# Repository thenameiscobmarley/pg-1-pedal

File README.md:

# PG-1 pedal

A DIY stereo audio pedal built around a **Daisy Seed3**, in a white Hammond 1590XX from Tayda. A 2.4" colour
touchscreen, four endless push-knobs, three footswitches and a chain of sound tools:

`in -> hum + hiss (with learn) -> input auto-level -> dynamic eq -> compressor -> multiband -> clarity + bass ->
saturation -> de-harsh -> stereo width -> takeback -> quiet loudness -> [bypass] -> ear + speaker safety -> out`

plus a visualizer, health checks (it tells you when something is wrong), 8 saved configs, a fair level-matched
A/B footswitch, and everything remembered over power-off.

The same core code runs on the pedal and in a **Carla / VST3 plugin** with a real-size 3D model of the pedal, so you
can try every screen and sound on a PC first.

## What's where

| Folder | |
|---|---|
| `PG-Pedal-1/01-Questions-and-Specs` | the spec |
| `PG-Pedal-1/02-Parts-and-Cart` | Tayda cart files + parts list (with the few parts Tayda doesn't sell) |
| `PG-Pedal-1/03-Drill-Template` | drill positions for drill.taydakits.com |
| `PG-Pedal-1/04-Top-Artwork` | the UV print (CMYK PDF for Tayda) and previews |
| `PG-Pedal-1/05-Wiring-and-Schematics` | **wiring-diagram.png** (every wire + both ground chains), layout drawings, WIRING.md |
| `PG-Pedal-1/06-Firmware-DaisySeed` | the firmware (`pg1/`) and its shared core (`pg1/core/`) |
| `PG-Pedal-1/10-Carla-Plugin` | the JUCE plugin with the 3D pedal |
| `PG-Pedal-1/11-Wiring-Bench` | `wiring-bench.html`: practise the wiring in a browser; a virtual pedal tells you what's wrong |
| `_Tools/pg_generate.py` | one script makes the drill table, artwork, drawings and the splash logo from the geometry at its top |
| `_Tools/tayda_upload.py` | uploads the drill + print designs to drill.taydakits.com (asks for your Tayda login) |
| `third_party/HardwareKit` | the 3D hardware UI module the plugin uses (Apache-2.0) |

## Building

Firmware (Linux):

```
git submodule update --init           # libDaisy v9.0.0 + DaisySP
cd PG-Pedal-1/06-Firmware-DaisySeed
(cd libDaisy && make -j"$(nproc)") && (cd DaisySP && make -j"$(nproc)")
cd pg1 && make -j"$(nproc)"           # build/pg1.bin (runs from the Daisy bootloader: see the firmware README)
```

Plugin: needs JUCE (https://juce.com, licensed separately).

```
cd PG-Pedal-1/10-Carla-Plugin
cmake -B build -DCMAKE_BUILD_TYPE=Release -DJUCE_PATH=/path/to/JUCE
cmake --build build -j"$(nproc)"
```

Artwork and drawings: `pip install fonttools`, then `python3 _Tools/pg_generate.py` (needs `rsvg-convert` and
ImageMagick for the PNG/PDF previews).

## Credits

- libDaisy and DaisySP by Electro-Smith (MIT), as git submodules
- Nunito font (SIL Open Font License, `_Tools/fonts/OFL.txt`)
- HardwareKit (Apache-2.0, `third_party/HardwareKit`)
- JUCE is not included; it has its own licence

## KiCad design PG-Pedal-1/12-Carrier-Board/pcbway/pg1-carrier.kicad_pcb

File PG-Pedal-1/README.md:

# PG-1: pg audio programmable stereo pedal (Daisy Seed3)

## Order it (3 steps)
1. **Parts:** upload `02-Parts-and-Cart/tayda-cart-import.csv` on the Tayda cart page (Import → Add from file → Replace current cart).
   Buy the Seed3 (with headers), a 9V adapter and solder separately (`02-Parts-and-Cart/BOM.md`).
2. **Drilled box + printed top:** run `python3 ../_Tools/tayda_upload.py`. It logs in to your drill.taydakits.com account and creates
   the drill template (17 holes + screen window + Seed3 window) and the UV print template for you. Then check both previews on the dashboard and create the order there.
   (By hand instead: `03-Drill-Template/DRILL-ORDER.md` + `04-Top-Artwork/UV-PRINT.md`.)

## Build it
`05-Wiring-and-Schematics/WIRING.md` has one table: every wire from each part to its Seed3 socket pin. It also shows the plug-in Seed3 cartridge in the left wall and covers the first flash.
`06-Firmware-DaisySeed/pg1.bin` is ready to flash: a stereo delay with auto-leveling that uses every control.

Using it with your Fifine SC3 (line out → pedal → headset): `USING-WITH-FIFINE-SC3.md`.

## Try it on your PC first
`10-Carla-Plugin/` is the PG-1 as a VST3 for Carla (and a standalone app): a 3D pedal with the **same screen, knobs, touch and sound** as the real one, because both run the same core code. Installed at `~/.vst3/PG-1 Pedal.vst3`.

## Folders
| Folder | What's inside |
|---|---|
| 01-Questions-and-Specs | final spec + your answers |
| 02-Parts-and-Cart | Tayda import CSV, full BOM with prices |
| 03-Drill-Template | drill.taydakits.com entry sheet, CSV, 1:1 paper template |
| 04-Top-Artwork | UV print PDF, editable SVG, mockup |
| 05-Wiring-and-Schematics | wiring, interior layout, depth check, perfboard drill guide |
| 06-Firmware-DaisySeed | libDaisy project + libDaisy v9.0.0 + DaisySP |
| 07-Datasheets | Seed3, screen, encoder, footswitch, jack |
| 08-Build-Photos | for your photos |
| 09-Parts-Visualizer | Parts Bench page + 3D web model |
| 10-Carla-Plugin | the PG-1 as a VST3 for Carla + standalone app |

All drawings and the artwork are generated from one script (`../_Tools/pg_generate.py`), so the holes and the print always match.

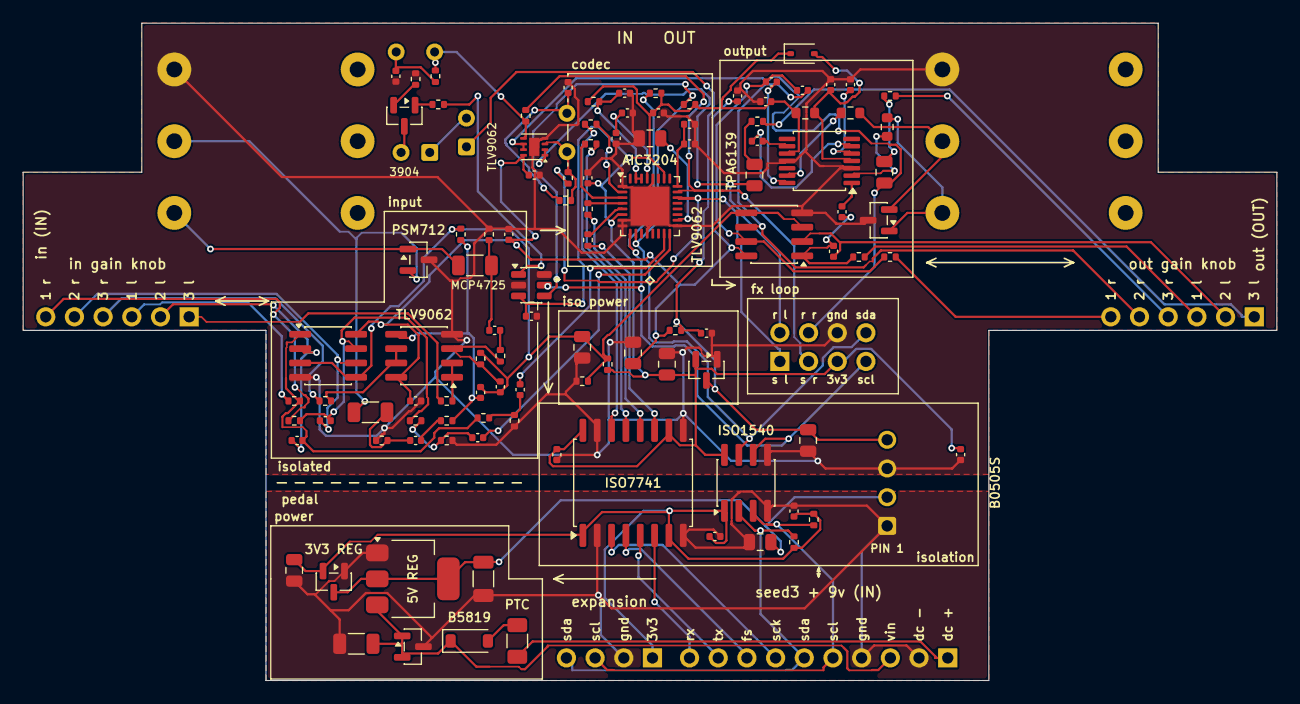
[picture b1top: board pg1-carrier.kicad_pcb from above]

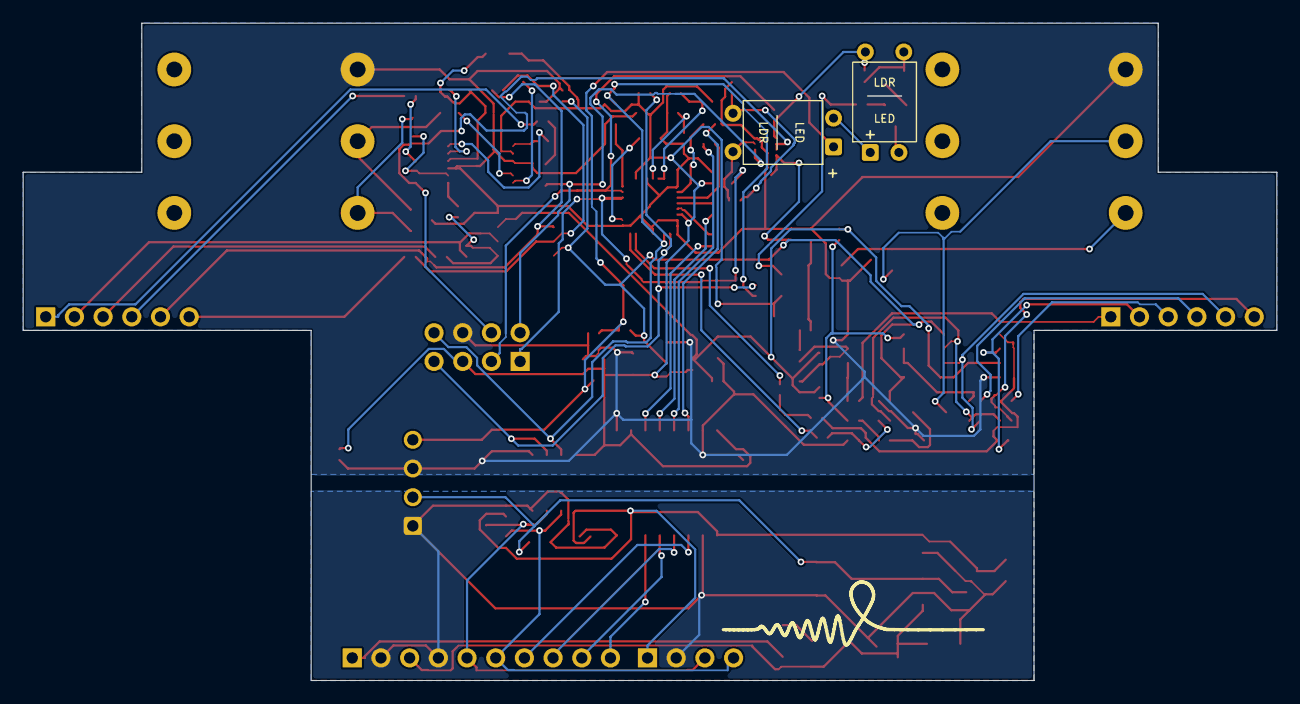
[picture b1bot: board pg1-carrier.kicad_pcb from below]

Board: 2 copper layers, 111.0 x 58.2 mm, 116 parts (2 on the bottom side), 86 nets.

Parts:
C1, C2: 22uF 25V; C_1206_3216Metric
C3, C14, C50, C60: 4.7uF; C_0805_2012Metric
C7, C8, C16, C17, C18: 10uF 25V; C_0805_2012Metric
C9, C10, C11, C12, C20, C22, C24, C25, C26, C27, C28, C30, C40, C82, C83: 100nF; C_0402_1005Metric
C15, C19, C21, C23, C32, C42, C51, C61, C70, C71, C72, C73: 1uF; C_0402_1005Metric
C31, C33, C41, C43, C52, C62: 100pF C0G; C_0402_1005Metric
C80, C85: 10uF; C_0402_1005Metric
D1: B5819W; D_SOD-123
D2, D61, D62: PSM712; SOT-23
D63: 1N4148WS; D_SOD-323
F1: PTC 300mA; Fuse_1206_3216Metric
J1: in; Jack_6.35mm_Neutrik_NMJ6HFD2_Horizontal
J2: out; Jack_6.35mm_Neutrik_NMJ6HFD2_Horizontal
J10: seed3 + 9v; PinHeader_1x10_P2.54mm_Horizontal
J19: pg-hp; PinHeader_1x06_P2.54mm_Horizontal
J20: pg-line; PinHeader_1x06_P2.54mm_Horizontal
J21: expansion; PinHeader_1x04_P2.54mm_Horizontal
J22: fx loop; PinHeader_2x04_P2.54mm_Vertical
OC1, OC2: LED+LDR; OPTO_PAIR_LED3_LDR5
Q1: MMBT3904; SOT-23
R3, R4, R9, R10, R80, R85: 4.7k; R_0402_1005Metric
R5: 10; R_0402_1005Metric
R6: 3.3k; R_0402_1005Metric
R7, R8, R35, R45: 10k; R_0402_1005Metric
R11, R12, R13, R14: 33; R_0402_1005Metric
R30, R40: 1k; R_1206_3216Metric
R31, R32, R41, R42: 1M; R_0402_1005Metric
R33, R43: 470k; R_0402_1005Metric
R34, R44: 20k; R_0402_1005Metric
R36, R37, R46, R47: 220; R_0402_1005Metric
R50, R60: 47; R_0603_1608Metric
R51, R52, R61, R62, R82: 1k; R_0402_1005Metric
R70: 1M; R_0603_1608Metric
R81, R86: 100k; R_0402_1005Metric
R83: 100; R_0402_1005Metric
U1: AMS1117-5.0; SOT-223-3_TabPin2
U2, U7: XC6206P332MR; SOT-23
U3: B0505S-1WR3; DCDC_SIP4_B0505S
U4: ISO7741; SOIC-16W_7.5x10.3mm_P1.27mm
U5: ISO1540; SOIC-8_3.9x4.9mm_P1.27mm
U8, U11, U12: TLV9062; SOIC-8_3.9x4.9mm_P1.27mm
U9: TLV320AIC3204; Texas_RHB0032E_VQFN-32-1EP_5x5mm_P0.5mm_EP3.45x3.45mm
U10: TPA6139A2; TSSOP-14_4.4x5mm_P0.65mm
U15: MCP4725; SOT-23-6
U16: TLV9062; Texas_DSG0008A_WSON-8-1EP_2x2mm_P0.5mm_EP0.9x1.6mm

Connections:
+3V3: C3.1, C9.1, C11.1, J21.1, R3.1, R4.1, U2.2, U4.1, U4.7, U5.1
+5V: C2.1, C7.1, U1.2, U2.3, U3.2
+9V: C1.1, D1.1, D2.1, D2.2, J10.3, U1.3
+9V_F: D1.2, F1.2
+9V_RAW: F1.1, J10.1
AVDD: C19.1, C20.1, U9.24
BCLK: R11.2, U9.2
BCLK_X: R11.1, U4.14
CIN2_L: C32.2, U9.15
CIN2_R: C42.2, U9.16
CRESET: C25.1, R8.2, U9.30, U9.31
DIN: R13.2, U9.4
DIN_X: R13.1, U4.12
DOUT: R14.1, U9.5
DOUT_X: R14.2, U4.11
DVDD: C21.1, C22.1, U9.29
FXR_L: C50.1, J22.2, U16.1, U16.2
FXR_R: C60.1, J22.4, U16.6, U16.7
GIN_A_L: J20.1, R36.2
GIN_A_R: J20.4, R46.2
GIN_B_L: J20.3, R37.1
GIN_B_R: J20.6, R47.1
GIN_W_L: C33.1, J20.2, U11.2
GIN_W_R: C43.1, J20.5, U11.6
GND: C1.2, C2.2, C3.2, C7.2, C9.2, C11.2, D2.3, J10.2, J10.4, J21.2, U1.1, U2.1, U3.1, U4.2, U4.8, U5.4
GOUT_A_L: J19.1, R51.2
GOUT_A_R: J19.4, R61.2
GOUT_B_L: J19.3, R52.1
GOUT_B_R: J19.6, R62.1
GOUT_W_L: C52.1, J19.2, U12.2
GOUT_W_R: C62.1, J19.5, U12.6
HPIN_L: C51.2, U10.1
HPIN_R: C61.2, U10.14
HPO_L: R50.1, U10.2
HPO_R: R60.1, U10.13
HP_CN: C70.2, U10.6
HP_CP: C70.1, U10.9
HP_ON: C73.1, D63.2, R70.2, U10.4
HP_VSS: C71.2, U10.5
IBIAS: C17.1, C31.2, C41.2, R6.2, R7.1, R33.2, R43.2, U11.3, U11.5, U12.3, U12.5
IGND: C8.2, C10.2, C12.2, C14.2, C15.2, C16.2, C17.2, C18.2, C19.2, C20.2, C21.2, C22.2, C23.2, C24.2, C25.2, C26.2, C27.2, C28.2, C71.1, C72.2, C73.2, C80.2, C82.2, C83.2, C85.2, D61.3, D62.3, J1.S, J2.S, J22.6, R7.2, R31.2, R35.2, R41.2, R45.2, R83.2, U3.3, U4.9, U4.15, U5.5, U7.1, U8.4, U9.1, U9.7, U9.8, U9.12, U9.17, U9.28, U9.33, U10.3, U10.11, U11.4, U12.4, U15.2, U15.6, U16.4, U16.9
IN_A_L: C30.1, R30.2, R31.1
IN_A_R: C40.1, R40.2, R41.1
IN_B_L: C30.2, R32.1
IN_B_R: C40.2, R42.1
IN_C_L: C31.1, R32.2, R33.1, U8.3
IN_C_R: C41.1, R42.2, R43.1, U8.5
IN_D_L: R36.1, U8.1, U8.2
IN_D_R: R46.1, U8.6, U8.7
IN_E_L: C32.1, R34.2, R35.1
IN_E_R: C42.1, R44.2, R45.1
IN_G_L: C33.2, R34.1, R37.2, U11.1
IN_G_R: C43.2, R44.1, R47.2, U11.7
ISCL: J22.7, R9.2, U5.6, U9.9, U15.5
ISDA: J22.8, R10.2, U5.7, U9.10, U15.4
ISO3V3: C10.1, C12.1, C14.1, C23.1, C24.1, C72.1, C82.1, D63.1, J22.5, R6.1, R8.1, R9.1, R10.1, R70.1, U4.10, U4.16, U5.8, U7.2, U9.6, U9.26, U10.10, U15.3
ISO5V: C16.1, C26.1, C27.1, C28.1, C83.1, R5.2, U8.8, U11.8, U12.8, U16.8
ISO5V_RAW: C8.1, C15.1, OC1.1, R5.1, U3.4, U7.3
JIN_L: D61.1, J1.T, R30.1
JIN_R: D61.2, J1.R, R40.1
JOUT_L: D62.1, J2.T, R50.2
JOUT_R: D62.2, J2.R, R60.2
LED_B: Q1.1, R82.2
LED_C: OC2.2, Q1.3
LED_DAC: R82.1, U15.1
LED_E: Q1.2, R83.1
LED_M: OC1.2, OC2.1
LO_L: J22.1, R80.1, U9.22
LO_R: J22.3, R85.1, U9.23
LVA_L: OC1.3, R80.2, R81.1, U16.3
LVA_R: OC2.3, R85.2, R86.1, U16.5
LVC_L: C80.1, OC1.4, R81.2
LVC_R: C85.1, OC2.4, R86.2
OUT_A_L: C50.2, R51.1
OUT_A_R: C60.2, R61.1
OUT_G_L: C51.1, C52.2, R52.2, U12.1
OUT_G_R: C61.1, C62.2, R62.2, U12.7
REF: C18.1, U9.18
SEED_FS: J10.8, U4.4
SEED_RX: J10.10, U4.6
SEED_SCK: J10.7, U4.3
SEED_SCL: J10.5, J21.3, R3.2, U5.3
SEED_SDA: J10.6, J21.4, R4.2, U5.2
SEED_TX: J10.9, U4.5
WCLK: R12.2, U9.3
WCLK_X: R12.1, U4.13

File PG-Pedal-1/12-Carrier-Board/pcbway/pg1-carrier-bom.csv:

Item #,Designator,Qty,Manufacturer,Mfg Part #,Description / Value,Package/Footprint,Type,Your Instructions / Notes
1,J10,1,any,,seed3 + 9v,PinHeader_1x10_P2.54mm_Horizontal,THT,"2.54 mm male header, any brand: please fit and solder"
2,J21,1,any,,expansion,PinHeader_1x04_P2.54mm_Horizontal,THT,"2.54 mm male header, any brand: please fit and solder"
3,F1,1,Littelfuse,1206L030/24NR,PTC 300mA,Fuse_1206_3216Metric,SMD,
4,D1,1,,B5819W,B5819W,D_SOD-123,SMD,
5,"D2,D61,D62",3,ProTek Devices,PSM712-LF-T7,PSM712,SOT-23,SMD,
6,"C1,C2",2,,CL31A226KAHNNNE,"ceramic capacitor 22uF 25V X7R 1206, 25 V or more",C_1206_3216Metric,SMD,
7,U1,1,AMS,AMS1117-5.0,AMS1117-5.0,SOT-223-3_TabPin2,SMD,
8,"U2,U7",2,Torex,XC6206P332MR-G,XC6206P332MR,SOT-23,SMD,
9,"C3,C14,C50,C60",4,,CL21A475KAQNNNE,"ceramic capacitor 4.7uF X7R 0805, 25 V or more",C_0805_2012Metric,SMD,
10,"R3,R4,R9,R10",4,any,,resistor 4.7k 1% 0402,R_0402_1005Metric,SMD,any brand with the same value and package
11,U3,1,Mornsun,B0505S-1WR3,B0505S-1WR3,DCDC_SIP4_B0505S,THT,"2.54 mm male header, any brand: please fit and solder"
12,"C7,C8,C16,C17,C18",5,,CL21A106KAYNNNE,"ceramic capacitor 10uF 25V X7R 0805, 25 V or more",C_0805_2012Metric,SMD,
13,U4,1,Texas Instruments,ISO7741DWR,ISO7741,SOIC-16W_7.5x10.3mm_P1.27mm,SMD,
14,"C9,C10,C11,C12,C20,C22,C24,C25,C26,C27,C28,C30,C40",13,any,,"ceramic capacitor 100nF X7R 0402, 25 V or more",C_0402_1005Metric,SMD,any brand with the same value and package
15,U5,1,Texas Instruments,ISO1540DR,ISO1540,SOIC-8_3.9x4.9mm_P1.27mm,SMD,
16,"C15,C19,C21,C23,C32,C42,C51,C61,C70,C71,C72,C73",12,any,,"ceramic capacitor 1uF X7R 0402, 25 V or more",C_0402_1005Metric,SMD,any brand with the same value and package
17,R5,1,any,,resistor 10 1% 0402,R_0402_1005Metric,SMD,any brand with the same value and package
18,"R6,R7,R8,R35,R45",5,any,,resistor 10k 1% 0402,R_0402_1005Metric,SMD,any brand with the same value and package
19,U9,1,Texas Instruments,TLV320AIC3204IRHBR,TLV320AIC3204,Texas_RHB0032E_VQFN-32-1EP_5x5mm_P0.5mm_EP3.45x3.45mm,SMD,
20,"R11,R12,R13,R14",4,any,,resistor 33 1% 0402,R_0402_1005Metric,SMD,any brand with the same value and package
21,"U8,U11,U12",3,Texas Instruments,TLV9062IDR,TLV9062,SOIC-8_3.9x4.9mm_P1.27mm,SMD,
22,J20,1,any,,pg-line,PinHeader_1x06_P2.54mm_Horizontal,THT,"2.54 mm male header, any brand: please fit and solder"
23,"R30,R40",2,any,,resistor 1k 1% 1206,R_1206_3216Metric,SMD,any brand with the same value and package
24,"R31,R32,R33,R41,R42,R43",6,any,,resistor 1M 1% 0402,R_0402_1005Metric,SMD,any brand with the same value and package
25,"R34,R44",2,any,,resistor 20k 1% 0402,R_0402_1005Metric,SMD,any brand with the same value and package
26,"R36,R37,R46,R47",4,any,,resistor 220 1% 0402,R_0402_1005Metric,SMD,any brand with the same value and package
27,"C33,C43,C52,C62",4,any,,"ceramic capacitor 100pF C0G 0402, 25 V or more",C_0402_1005Metric,SMD,any brand with the same value and package
28,"R51,R52,R61,R62",4,any,,resistor 1k 1% 0402,R_0402_1005Metric,SMD,any brand with the same value and package
29,"R50,R60",2,any,,resistor 1 1% 0603,R_0603_1608Metric,SMD,any brand with the same value and package
30,J22,1,any,,fx loop,PinHeader_2x04_P2.54mm_Vertical,THT,"2.54 mm male header, any brand: please fit and solder"
31,J19,1,any,,pg-hp,PinHeader_1x06_P2.54mm_Horizontal,THT,"2.54 mm male header, any brand: please fit and solder"
32,U10,1,Texas Instruments,TPA6139A2PWR,TPA6139A2,TSSOP-14_4.4x5mm_P0.65mm,SMD,
33,R70,1,any,,resistor 470k 1% 0603,R_0603_1608Metric,SMD,any brand with the same value and package
34,"J1,J2",2,Neutrik,NMJ6HFD2,6.35 mm stereo PCB jack,Jack_6.35mm_Neutrik_NMJ6HFD2_Horizontal,THT,please fit and solder

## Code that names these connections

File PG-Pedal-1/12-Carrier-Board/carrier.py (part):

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# Seed3 pin -> what it is (05-Wiring-and-Schematics/WIRING.md). v3: SAI2 on 32-35 + I2C1 on 12/13; the Seed3's own
# audio pins (16-19) are not used.
SEED = {1: "LCD_RESET", 2: "PG1_A", 3: "PG1_B", 4: "PG1_PUSH", 5: "PG2_A", 6: "PG2_B", 7: "PG2_PUSH", 8: "LCD_CS",
        9: "LCD_SCK", 10: "PGC", 11: "LCD_SDI", 12: "SEED_SCL", 13: "SEED_SDA", 14: "PG3_A", 15: "PG3_B",
        16: "NC_AUDIO_IN_1", 17: "NC_AUDIO_IN_2", 18: "NC_AUDIO_OUT_1", 19: "NC_AUDIO_OUT_2", 20: "AGND", 21: "3V3A",
        22: "PG3_PUSH", 23: "LCD_LED", 24: "PGA", 25: "PGB", 26: "PG4_A", 27: "PG4_B", 28: "PG4_PUSH",
        29: "T_CLK", 30: "T_CS", 31: "T_DIN", 32: "SEED_RX", 33: "SEED_TX", 34: "SEED_FS", 35: "SEED_SCK",
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P("R4", "4.7k", R0603, "", {1: "+3V3", 2: "SEED_SDA"})

# ================================================================ THE BARRIER (each part has one half on each side)
P("U3", "B0505S-1WR3", "PG1:DCDC_SIP4_B0505S", "B0505S-1WR3", {1: "GND", 2: "+5V", 3: "IGND", 4: "ISO5V_RAW"},
  "isolated 5 V, 1 W, 1 kV")
P("C7", "10uF 25V", C0805, "CL21A106KAYNNNE", {1: "+5V", 2: "GND"})
P("C8", "10uF 25V", C0805, "CL21A106KAYNNNE", {1: "ISO5V_RAW", 2: "IGND"})
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  {1: "IGND", 2: "BCLK", 3: "WCLK", 4: "DIN", 5: "DOUT", 6: "ISO3V3", 7: "IGND", 8: "IGND", 9: "ISCL", 10: "ISDA",
   12: "IGND", 15: "CIN2_L", 16: "CIN2_R", 17: "IGND", 18: "REF", 24: "AVDD",
   22: "LO_L", 23: "LO_R", 26: "ISO3V3", 28: "IGND", 29: "DVDD", 30: "CRESET", 31: "CRESET", 33: "IGND"},
  "pins: 1 MCLK (unused: PLL from BCLK), 8 MFP3 grounded, 12 SPI_SELECT=0 (I2C), 30 LDO_SELECT high (DVDD LDO on):\n"
  "  joined to the reset pin's pull-up next to it, so both come up together; the firmware then resets it over I2C")
P("C18", "10uF 25V", C0805, "CL21A106KAYNNNE", {1: "REF", 2: "IGND"}, "REF")
P("C19", "1uF", C0603, "", {1: "AVDD", 2: "IGND"})
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    P(f"C{b+1}", "100pF C0G", C0603, "", {1: n("IN_C"), 2: "IBIAS"},
      "NOT FITTED (DNP in make_jlc / make_bom): on the 500 k divider it was a 3.2 kHz low-pass (found by the simulation)")
    P(f"R{b+4}", "20k", R0603, "", {1: n("IN_G"), 2: n("IN_E")},
      "THE INPUT CLAMP: 20k / 10k (and the codec's 20k) keep the codec's pin inside its safe window (-0.3 .. AVDD + 0.3)"
      " whatever the pg-line op-amp does, even slammed rail to rail after a long hit: ngspice -0.02 .. +1.85 V (12k: -0.42)")
    P(f"R{b+5}", "10k", R0603, "", {1: n("IN_E"), 2: "IGND"})
    P(f"C{b+2}", "1uF", C0603, "", {1: n("IN_E"), 2: n("CIN2")})
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P("J19", "pg-hp", HDR_RA(6), "", {1: "GOUT_A_L", 2: "GOUT_W_L", 3: "GOUT_B_L", 4: "GOUT_A_R", 5: "GOUT_W_R", 6: "GOUT_B_R"},
  "isolated side: pg-hp, centre-detent dual 10k LINEAR pot, pot pins 3 / 2 / 1 per gang on header pins 1 / 2 / 3 (clockwise end first: right = more)")
P("U10", "TPA6139A2", "Package_SO:TSSOP-14_4.4x5mm_P0.65mm", "TPA6139A2PWR",
  {1: "HPIN_L", 2: "HPO_L", 3: "IGND", 4: "HP_ON", 5: "HP_VSS", 6: "HP_CN", 9: "HP_CP", 10: "ISO3V3", 11: "IGND",
   12: "NC_GAIN", 13: "HPO_R", 14: "HPIN_R"}, "headphone / line driver, x-2 (gain pin open): +6 dB at the top of pg-hp")
P("C70", "1uF", C0603, "", {1: "HP_CP", 2: "HP_CN"}, "charge-pump flying cap")
P("C71", "1uF", C0603, "", {1: "IGND", 2: "HP_VSS"}, "charge-pump hold cap")
P("C72", "1uF", C0603, "", {1: "ISO3V3", 2: "IGND"}, "at the TPA6139A2")
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
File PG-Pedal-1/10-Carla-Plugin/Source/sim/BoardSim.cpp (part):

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        {
            const double vdd = v[2] - v[3];
            const double on  = Sg(p0[2] - p0[3] - 2.75, 0.2);
            const double un  = Sg(p0[4] - p0[3] - 1.2, 0.03); // (HP_ON is a logic input: muted or not)
            const double lim = std::max(0.05, vdd - 0.3);
            const double vt  = v[3] + un * Clamp(-2.0 * (v[0] - v[3]), -lim, lim, 0.02);
            const double io  = on * (vt - v[1]) / e.p[1];
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    };
    const bool p5   = rail("+5V", "GND", 4.5, 5.6, "the isolated converter");
    const bool p33  = rail("+3V3", "GND", 3.0, 3.6, "the isolators' pedal side");
    const bool i5   = rail("ISO5V_RAW", "IGND", 4.0, 6.0, "the isolated side");
    const bool i33  = rail("ISO3V3", "IGND", 3.0, 3.6, "the codec / headphone amp");
    (void) p5, (void) i5;
    // the Seed3
    const int  sv = node("SEED.39"), sg = node("SEED.40");
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    else if(seedOn && !sameGnd)
        F(1, "wiring", "the Seed3's ground isn't the board's ground: wire gnd to Seed3 pin 40");
    auto linked = [&](const char* seedPin, const char* net) { return node(seedPin) == nd(net); };
    const bool i2c = seedOn && sameGnd && p33 && i33 && linked("SEED.12", "SEED_SCL") && linked("SEED.13", "SEED_SDA");
    const bool clk = seedOn && sameGnd && p33 && i33 && linked("SEED.35", "SEED_SCK") && linked("SEED.34", "SEED_FS");
    i2sOut          = clk && linked("SEED.33", "SEED_TX");
    i2sIn           = clk && linked("SEED.32", "SEED_RX");
    codecPowered    = i33 && vOf("CRESET", "IGND") > 2.0;
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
